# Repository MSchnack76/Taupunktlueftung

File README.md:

> [!WARNING] 
> Repository umgezogen auf die Codeberg-Plattform! Neue Versionen unter [Taupunktlueftung bei Coderberg](https://codeberg.org/MSchnack76/Taupunktlueftung.git)

# Taupunktlüftung

## Überblick
Realisierung einer Taupunkt gesteuerten Lüftung, die die Lüftung nur dann einschaltet, wenn die Taupunkt-Temperatur der Umgebungsluft (Abluftraum - bspw. außerhalb des Gebäudes) deutlich niedriger ist, als die Taupunkt-Temperatur des Raumes, der be- bzw. entlüftet werden soll.

## Elektrotechnischer Hinweis & DISCLAIMER
Ich mache an dieser Stelle darauf aufmerksam, dass diese Steuerung an einer 230V/50Hz Netzspannung betrieben wird. Es sind die einschlägigen Vorschriften für das Arbeiten, Anschließen und Betreiben einer elektrischen Anlage an 230V/50Hz zu beachten! Personen, die weder Erfahrung noch die nötige Ausbildung in der Elektrotechnik besitzen rate ich daher ausdrücklich vom Nachbau ab.
Dies ist ein Hobby-Projekt mit keinerlei Zualssung für den regelmäßigen Betrieb / Anschluss am 230V/50Hz Netz.

Alle Daten und Dateien sind nach bestem Wissen und Gewissen erstellt, haben jedoch PROTOTYPEN-Status!
Daher übernehme ich keinerlei Verantwortung für die Korrektheit der Daten und keinerlei Verantwortung für irgendwelche Schäden, die aus einem evt. Nachbau resultieren!
Diese Dokumentation ist ein rein privates Versuchs-Objekt!

## Umsetzung
### Elektronik & Leiterplatte (PCB)
Für die Steuerung kommt ein Microcontroller vom Typ Atmel 328P zum Einsatz. Der Lüfter wird über einen Optokoppler MOC3021M / TRIAC BTA 16-600 angesteuert, die mit Peripherie-Beschaltung ein Solid-State-Relais bilden.
Die Messung der Temperaturen und relativen Luftfeuchten des Abluftraumes / zu belüftenden Raumes wird über Sensoren vom Typ GY-21 HTU21 realisiert, die über einen I²C-Multiplexer TCA9543ADR an den Microcontroller angebunden werden.

Eine Daten-Ausgabe findet auf einem LCD-Display (DOT-Matrix) mit 4 Zeilen zu je 20 Zeichen (4x20) statt, welches über I²C an den Microcontroller angebunden wird. Die Hintergrundbeleuchtung des Displays kann über einen Kipptaster aktiviert werden. Der gleiche Kipptaster löst in der anderen Richtung einen Reset des Mikrocontrollers aus.

Ein Dreh-Encoder mit Tast-Funktion wird für die Menu-Steuerung eingesetzt. Das Menu und die Einstellungen werden über das LCD-Display angezeigt. Folgende Parameter können über das Menu verändert und entsprechend gesetzt werden:
a) Delta Taupunkt Schaltschwelle für das Einschalten des Lüfters (Minimales Delta zwischen Taupunkt innen und außen)
   --> Vorgabewert 5°C
b) Hystere Delta Taupunkt für das Abschalten des Lüfters
   --> Vorgabewert 1°C
c) Minimale Innenraum-Temperatur (unterhalb der Temperatur findet keine Lüftung statt)
   --> Vorgabewert 3°C
d) Minimale Außen-Temperatur (unterhalb der Temperatur findet keine Lüftung statt)
   --> Vorgabewert -10°C

Über einen Kipp-Schalter kann die Steuerung in den
1. dauerhaft EIN-Modus (Lüfter läuft ständig)
2. deaktivierten Modus (Lüfter ist dauerhaft deaktiviert)
3. in den Automatik-Modus (Taupunkt gesteuerte Be- bzw. Entlüftung)
versetzt werden.

Die Leiterplatte ist für eine Stromaufnahme von 5A bei 230VAC ausgelegt und wird über eine entsprechende Sicherung 5x20mm, 5A mittelträge vor Überstrom geschützt. Der Kleinspannungsbereich auf der PCB ist zusätzlich über eine Sicherung 5x20mm, 500mA flink abgesichert.

Der Aufbau findet bewusst im aktuellen Stadium der Entwicklung mit THT-Bauteilen (mit Ausnhame des I²C-Multiplexers, den es nur als SMD SO-14 Package gibt) statt.

### Gehäuse
Das Gehäuse wurde über eine CAD-Software konstruiert und mittels 3D-Druck erstellt. Alle Komponenten wurden im 3D-Modell eingefügt.
Die Leiterplatte sitzt auf Distanzbolzen des Gehäuses, das Display ist an der Rückseite des Deckels befestigt. Die Konnektivität der Sensoren ist über D-SUB Buchsen / Stecker realisiert.

### Verwendete Software
|Programm   |Verwendung                               |Dateiformat |
|-----------|-----------------------------------------|------------|
| [FreeCAD](https://www.freecad.org)    | CAD Konstruktionen | .FCStd |
| 3D-Druck | Standard Tessellation Language | .stl |
| [KiCAD](https://www.kicad.org/)| Schaltpläne | .kicad_sch |
| [KiCAD](https://www.kicad.org/)| PCB Layout | .kicad_pcb |
| [KiCAD](https://www.kicad.org/)| Projekt | .kicad_pro |
| [VisualStudioCode](https://code.visualstudio.com/)| Programmcode | .h und .cpp |
| [PlatformIO](https://platformio.org/)| Programmcode | .h und .cpp |
| [LibreOffice](https://www.libreoffice.org/)| Stückliste | .ods |

### PCB Hersteller
Ich bin sehr zufrieden mit dem deutschen PCB-Hersteller AISLER Germany GmbH mit Sitz in Aachen.

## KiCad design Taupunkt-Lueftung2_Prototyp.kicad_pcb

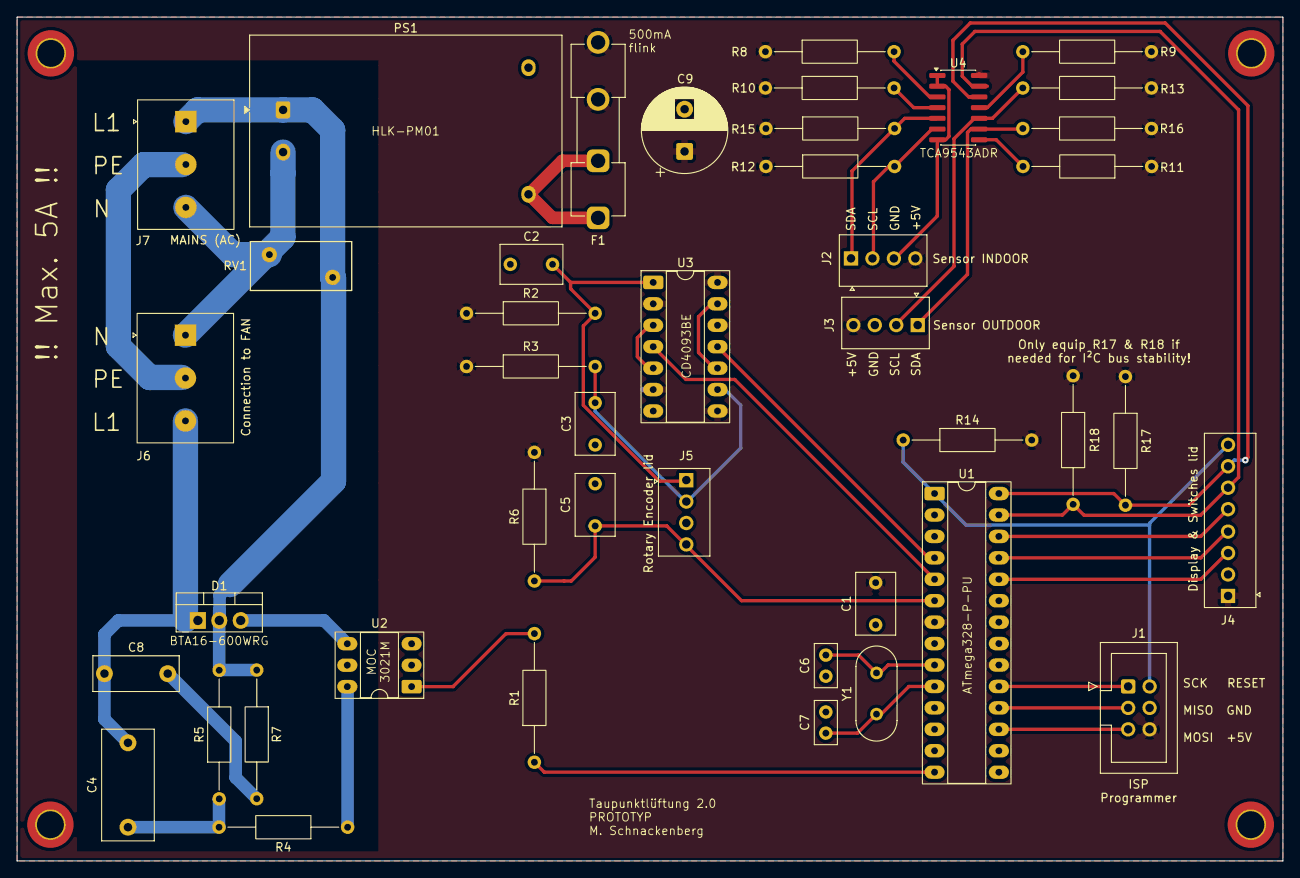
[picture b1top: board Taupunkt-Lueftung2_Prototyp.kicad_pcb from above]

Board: 2 copper layers, 150.0 x 100.0 mm, 43 parts (0 on the bottom side), 39 nets.

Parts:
C1, C2, C3, C5: 100n; C_Rect_L7.2mm_W4.5mm_P5.00mm_FKS2_FKP2_MKS2_MKP2
C4: 47nF; C_Rect_L13.0mm_W6.0mm_P10.00mm_FKS3_FKP3_MKS4
C6, C7: 22p; C_Disc_D5.0mm_W2.5mm_P2.50mm
C8: 10nF; C_Rect_L10.0mm_W4.0mm_P7.50mm_FKS3_FKP3
C9: 1000µF/16V; CP_Radial_D10.0mm_P5.00mm
D1: BTA16-600SWRG; TO-220-3_Vertical
F1: 500mA; Fuseholder_Clip-5x20mm_Eaton_1A5601-01_Inline_P20.80x6.76mm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
J1: ISP; IDC-Header_2x03_P2.54mm_Vertical
J2: Sensor Indoor; Connector_Encoding_4x1_MPE_428-1-004-0-T-KS0
J3: Sensor Outdoor; Connector_Encoding_4x1_MPE_428-1-004-0-T-KS0
J4: Display & Switches; Connector_Encoding_8x1_MPE_428-1-008-0-T-KS0
J5: Rotary Encoder; Connector_Encoding_4x1_MPE_428-1-004-0-T-KS0
J6: Ventilator (AC); Connector_Screwterminal_3x1_MetzConnect_31073103
J7: Mains (AC 230V); Connector_Screwterminal_3x1_MetzConnect_31073103
PS1: HLK-PM01; Converter_ACDC_Hi-Link_HLK-PMxx
R1, R4: 360; R_Axial_DIN0207_L6.3mm_D2.5mm_P15.24mm_Horizontal
R2, R3, R6: 100K; R_Axial_DIN0207_L6.3mm_D2.5mm_P15.24mm_Horizontal
R5: 470; R_Axial_DIN0207_L6.3mm_D2.5mm_P15.24mm_Horizontal
R7: 39; R_Axial_DIN0207_L6.3mm_D2.5mm_P15.24mm_Horizontal
R8, R9, R10, R11, R14: 10k; R_Axial_DIN0207_L6.3mm_D2.5mm_P15.24mm_Horizontal
R12, R13, R15, R16, R17, R18: 4k7; R_Axial_DIN0207_L6.3mm_D2.5mm_P15.24mm_Horizontal
RV1: 250 VAC; RV_Disc_D12mm_W5.8mm_P7.5mm
U1: ATmega328-P-PU; DIP-28_W7.62mm_Socket_LongPads
U2: MOC3021M; DIP-6_W7.62mm_Socket_LongPads
U3: CD4093BE; DIP-14_W7.62mm_Socket_LongPads
U4: TCA9543ADR; SOIC-14_3.9x8.7mm_P1.27mm
Y1: HC49/4H 16MHz; Crystal_HC49-4H_Vertical

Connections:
+5V: C1.1, C9.1, F1.2, J1.6, J2.4, J3.4, J4.1, R2.1, R3.1, R6.1, R8.1, R9.1, R10.1, R11.1, R12.1, R13.1, R14.2, R15.1, R16.1, R17.1, R18.1, U1.7 (VCC), U1.20 (AVCC), U3.2, U3.6, U3.8, U3.12, U3.14 (VCC), U4.14 (VCC)
/AC_Line_L1: D1.2 (A2), J7.1, PS1.1 (AC/L), R5.2, R7.1, RV1.1
/AC_Line_N: J6.1, J7.3, PS1.2 (AC/N), RV1.2
/AC_Line_PE: J6.2, J7.2
/Crystal_1: C6.2, U1.9 (XTAL1/PB6), Y1.2
/Crystal_2: C7.1, U1.10 (XTAL2/PB7), Y1.1
/Display_Lightning: J4.5, U1.26 (PC3)
/I²C_SCL: J4.7, R17.2, U1.28 (PC5), U4.12 (SCL)
/I²C_SCL_INSIDE: J2.2, R12.2, U4.6 (SC0)
/I²C_SCL_OUTSIDE: J3.2, R13.2, U4.10 (SC1)
/I²C_SDA: J4.6, R18.2, U1.27 (PC4), U4.13 (SDA)
/I²C_SDA_INSIDE: J2.1, R15.2, U4.5 (SD0)
/I²C_SDA_OUTSIDE: J3.1, R16.2, U4.9 (SD1)
/MISO: J1.3, U1.18 (PB4)
/MOSI: J1.5, U1.17 (PB3)
/RESET: J1.2, J4.8, R14.1, U1.1 (~RESET/PC6)
/Rotary_Encode_A: C3.1, J5.2, R3.2, U3.9
/Rotary_Encode_A_debounced: U1.4 (PD2), U3.11
/Rotary_Encode_B: C2.1, J5.1, R2.2, U3.1
/Rotary_Encode_B_debounced: U1.5 (PD3), U3.4
/Rotary_Encoder_Button: C5.1, J5.4, R6.2, U1.6 (PD4)
/SCK: J1.1, U1.19 (PB5)
/Triac_Gate: D1.3 (G), U2.4
/Ventilation_OFF: J4.4, U1.25 (PC2)
/Ventilation_ON: J4.3, U1.24 (PC1)
/Ventilation_Relais: R1.1, U1.14 (PB0)
/Ventilator_AC: C4.2, C8.2, D1.1 (A1), J6.3
GND: C1.2, C2.2, C3.2, C5.2, C6.1, C7.2, C9.2, J1.4, J2.3, J3.3, J4.2, J5.3, PS1.3 (-Vout), U1.8 (GND), U1.22 (GND), U2.2, U3.7 (GND), U4.1 (A0), U4.2 (A1), U4.7 (GND)
unnamed: C4.1, R4.2, R5.1
unnamed: C8.1, R7.2
unnamed: F1.1, PS1.4 (+Vout)
unnamed: R1.2, U2.1
unnamed: R4.1, U2.6
unnamed: U3.3, U3.5
unnamed: U3.10, U3.13
unnamed: R10.2, U4.4 (~INT0)
unnamed: R11.2, U4.8 (~INT1)
unnamed: R9.2, U4.11 (~INT)
unnamed: R8.2, U4.3 (~RESET)

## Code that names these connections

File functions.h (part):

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#define GLOBALS_

/* Definition der verwendeten Microcontroller Pins */
#define RELAISPIN 8                         // PB0, 328P Pin 14 - Luefter schalten
#define MAN_EIN 15                          // PC1, 328P Pin 24 - Schalter Ein - Auto - Aus
#define MAN_AUS 16                          // PC2, 328P Pin 25 - Schalter Ein - Auto - Aus
#define LICHT 17                            // PC3, 328P Pin 26 - Taster für LCD-Display Belechtung
#define ENCODER_A 2                         // PD2, 328P Pin 04 - Dreh-Encoder Pin A
#define ENCODER_B 3                         // PD3, 328P Pin 05 - Dreh-Encoder Pin B
#define MENUBUTTON 4                        // PD4, 328P Pin 06 - Dreh-Encoder Taster

/* Schalten des Relais über N-Feld-Effekt-Transistor, Vorwiderstand und die Masse | VCC liegt fix an der Relais-Spule an */
/* Definition der Relais-Zustände für Programmierung                                                                     */
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
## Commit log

2025-08-22 Create LICENSE
2025-08-22 Add CAD-file for housing of electronics
    CAD-data-file (FreeCAD format) for the housing of the electronics including lower part and lid with cutouts / holes for cable inputs, display, switches.
2025-08-22 Add housing lower part STEP file for 3D-printing
    STEP file for 3D-printing of housing lower part based on the CAD file
2025-08-22 Add housing lid STEP file for 3D-printing
    STEP file for 3D-printing of housing lid based on the CAD file
2025-08-22 Update README.md
    Übersicht der verwendeten Software hinzugefügt
2026-04-02 Delete Taupunkt_Lueftung_Gehaeuse-Deckel.step
    Falsche Datei
2026-04-02 Delete Taupunkt_Lueftung_Gehaeuse-Unterteil.step
    Falsche Datei
2026-04-02 Delete Taupunkt_Lueftung_Gehaeuse.FCStd
    Falsche Datei
2026-04-02 Update README.md
    Update
2026-06-09 Update README.md
    Information Umzug zu Codeberg
